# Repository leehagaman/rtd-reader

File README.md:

# 16 Channel PT1000 Reader

This project describes an Arduino shield which allows the reading of up to 16 PT1000 2 wire RTD temperature sensors, and communicate that information to a computer. It also has two digital outputs, designed to control relays which can turn heaters on and off. This design allows the Arduino to autonomously control the heaters, ensuring consistent temperature control even if the main computer loses connection.

## Getting Started

### Materials

To make the Arduino shield, you need the following items:

- 1 Arduino Due or Arduino Mega (with corresponding cable, and power supply if you'd like continued operation in the event of a computer failure)
- 1 Printed Circuit Board (see .brd file)
- 1 LM324 Op Amp chip [link](https://www.digikey.com/product-detail/en/texas-instruments/LM324N/296-1391-5-ND/277627)
- 3 CD4052B Multiplexing chips [link](https://www.digikey.com/product-detail/en/texas-instruments/CD4051BE/296-2057-5-ND/67305)
- 18 0.1" double right angle connectors [link](https://www.digikey.com/products/en?mpart=PREC040SFAN-RC&v=35)
- 40 0.1" straight connectors [link](https://www.digikey.com/products/en?mpart=PREC040SFAN-RC&v=35)
- 16 1kΩ resistors
- 6 amplification resistors (optional, see "choosing resistors" section)

### Choosing Resistors

For the 16 1kΩ resistors, you can measure and record their specific resistances after installation for increased accuracy, so there is no special process to choose them.

The Arduino will constantly measure an unamplified temperature, which has a resolution which varies from about 0.1°C near -200°C, to about 1°C near 40°C (this is calculated using 10 bit resolution, an Arduino Due can be configured to use 12 bits instead, giving 100 times finer resolution). 

<p align="center">Serial monitor output comparing amplified and unamplified measurements. These curves were obtained by pinching a PT1000 with my fingers and then releasing. The overall offset can likely be fixed with calibration. (Image will be updated to a cleaner one soon.)</p>

To improve this resolution, the Arduino will also measure an amplified temperature, which lets you effectively "zoom in" on an specific temperature range (see above comparison). There is a several step process to determine the ideal resistors for a given temperature range of interest.

1. Decide on T<sub>min</sub> and T<sub>max</sub>, the minimum and maximum temperatures you plan to measure with your amplified circuit.
2. Calculate the R<sub>min</sub> and R<sub>max</sub>, the corresponding minimum and maximum PT1000 resistances (use something like [this table](https://web.mst.edu/~cottrell/ME240/Resources/Temperature/RTD%20table.pdf))
3. Calculate V<sub>min</sub> and V<sub>max</sub>, the corresponding voltages read by the Arduino. Use the formula V=R/(R+1000Ω)*(3.3 Volts).
4. We have our unamplified voltage range, and we will use our amplifier to convert this to our desired voltage range of 0.1V-1.7V (the op-amp only gets within 1.5V of the maximum, so the measurable range is 0-1.8V, and we give each side 0.1V of buffer). So, the desired amplification factor is A=(V<sub>max</sub>- V<sub>min</sub>)/(1.6 Volts). We also have an ideal offset voltage V<sub>off</sub>  equal to V<sub>min</sub>.
5. Now that we have ideal A and V<sub>off</sub> values chosen, we must modify them to make their values easy to construct with available resistors. We must choose resistors with resistance values R<sub>1</sub>, R<sub>2</sub>, R<sub>off1</sub>, and R<sub>off2</sub> such that A=R<sub>2</sub>/R<sub>1</sub> and  V<sub>off</sub>=V<sub>min</sub>. It is perfectly fine to decrease A and adjust V<sub>off</sub> in order to accomplish this without having to use nonstandard resistors, it will just slightly change the range of voltages, which is why we gave each side 0.1V of buffer in step 4. 
6. To check that your resistance values will work as expected, recalculate your amplified voltage range. The amplified voltage will be V<sub>amp </sub>= R<sub>2</sub>/R<sub>1</sub> * (V - (3.3 Volts) * R<sub>off2</sub> / (R<sub>off1</sub> + R<sub>off2</sub> )) where V is the unamplified voltage. It's a good idea to use that formula to double check that the amplified voltage will stay in the range 0 to 1.7 Volts for the expected unamplified voltages from step 3.

Now that we have our desired resistor values, R<sub>1</sub>, R<sub>2</sub>, R<sub>off1</sub>, and R<sub>off2</sub>, we need to choose resistors with those resistance values. We need a pair of resistors, R<sub>amp1</sub> and R<sub>amp2</sub>, to have resistances as close as possible to R<sub>1</sub>, and another pair R<sub>amp3</sub> and R<sub>amp4</sub>, to have resistances as close as possible to R<sub>amp1</sub> and R<sub>2</sub>. It is worth taking some time to match the resistances of each pair, as the linearity of the amplifier depends on their values being equal. Once you have also chosen R<sub>off1</sub> and R<sub>off2</sub>, take the time to measure and record the resistances of each resistor, as their precise values are used by the arduino program to reconstruct the temperature from the amplified voltage, and the resistances cannot be simply measured after soldering.

### Assembly

Soldering can be done in any order, but I recommend soldering the pin connectors last as they can give you less room to solder the 16 1kΩ resistors.

### Program Modification

In the Arduino file, you should modify the parameters to correspond to your measured resistances and active channels. You can also switch between LabVIEW output and serial monitor output.

I plan to improve the readability of the arduino code once the LabVIEW integration is finalized.

### Calibration

Will be updated soon. I should be able to use a known temperature to calibrate the temperature measurements, as well as matching the amplified measurement to the unamplified measurement just using the ambient room temperature.

## LabVIEW Integration

Will be updated soon. I plan to support output of temperature as well as input of desired temperature windows.

## Acknowledgments

* Domenico Franco helped me iterate the PCB design.

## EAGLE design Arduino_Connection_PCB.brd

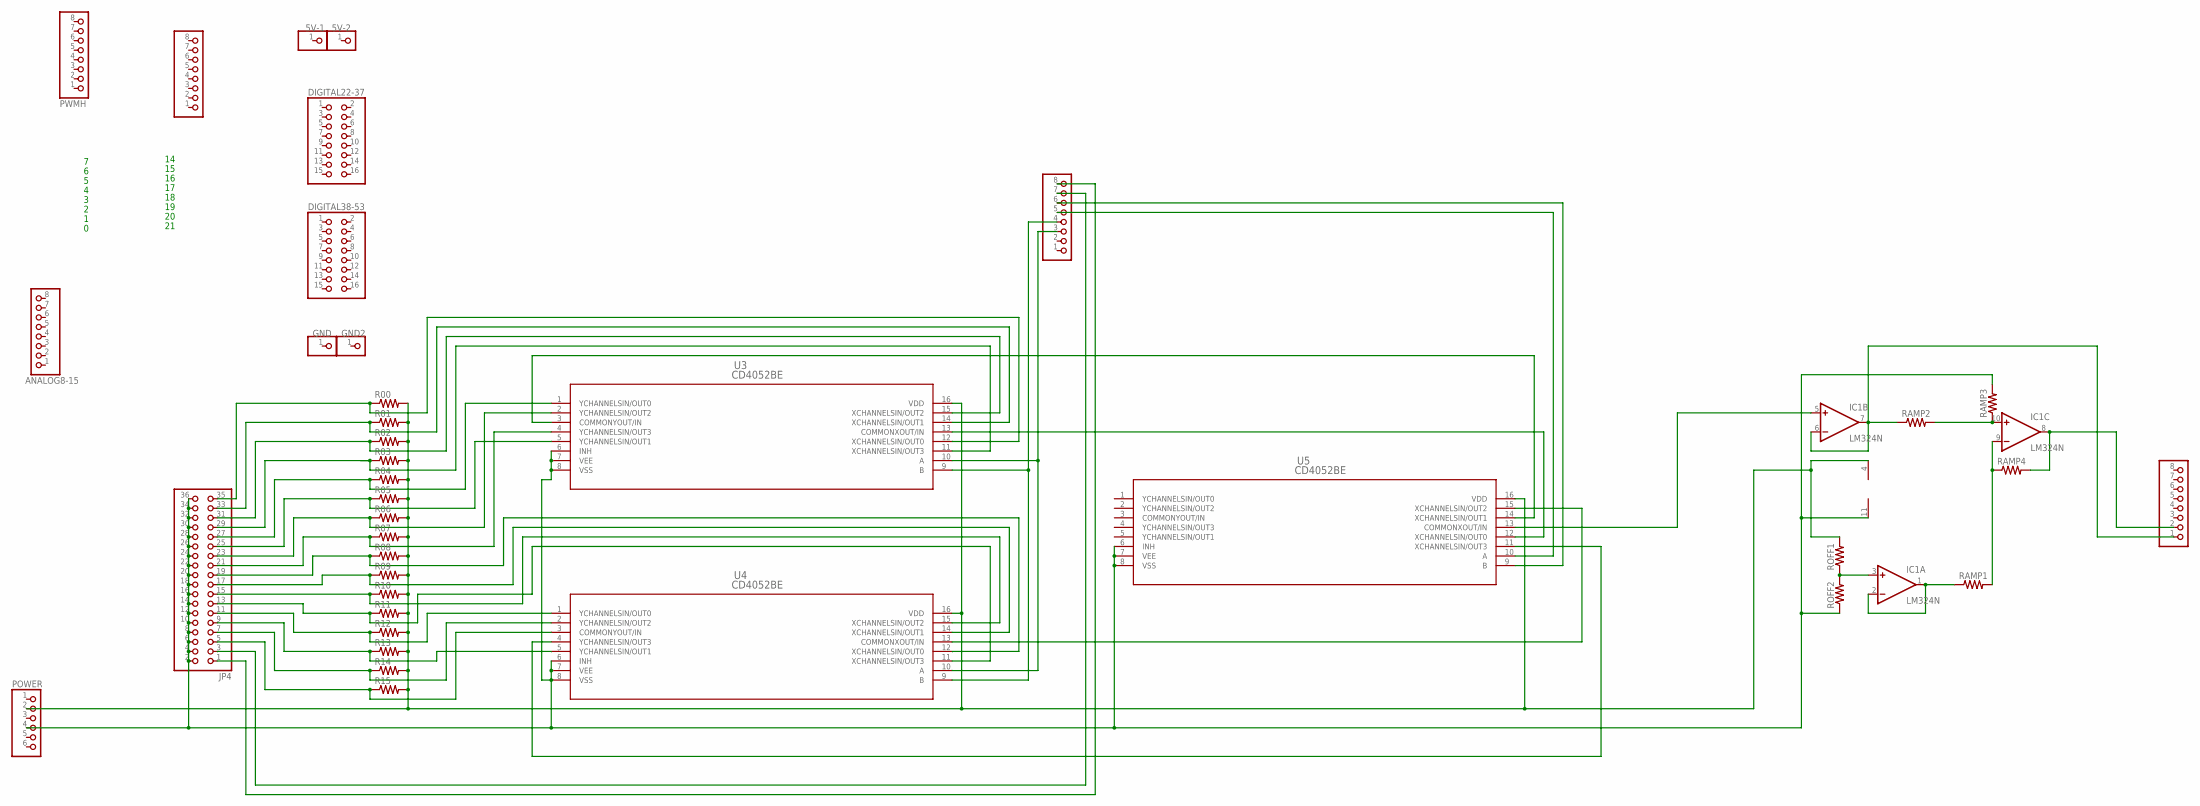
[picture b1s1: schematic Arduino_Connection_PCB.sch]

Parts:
5V-1, 5V-2: PINHD-1X1; 1X01
ANALOG0-7, ANALOG8-15: PINHD-1X8; 1X08
COMMUNICATION: PINHD-1X8; 1X08
DIGITAL22-37, DIGITAL38-53: PINHD-2X8; 2X08
GND, GND2: PINHD-1X1; 1X01
IC1: LM324N; DIL14
JP4: PINHD-2X18/90; 2X18/90
POWER: PINHD-1X6; 1X06
PWMH: PINHD-1X8; 1X08
PWML: PINHD-1X8; 1X08
R00, R01, R02, R03, R04, R05, R06, R07, R08, R09, R10, R11, R12, R13, R14, R15: R-US_0204/7; 0204/7
RAMP1, RAMP2, RAMP3, RAMP4: R-US_0204/7; 0204/7
ROFF1, ROFF2: R-US_0204/7; 0204/7
U3, U4, U5: CD4052BE; N16

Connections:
unnamed: IC1.5 (+IN), U5.13 (COMMONXOUT/IN)
unnamed: ANALOG0-7.1, IC1.6 (-IN), IC1.7 (OUT), RAMP2.1
unnamed: JP4.3, PWML.7
unnamed: JP4.1, PWML.8
unnamed: IC1.3 (+IN), ROFF1.1, ROFF2.2
unnamed: IC1.11 (V-), JP4.2, JP4.4, JP4.6, JP4.8, JP4.10, JP4.12, JP4.14, JP4.16, JP4.18, JP4.20, JP4.22, JP4.24, JP4.26, JP4.28, JP4.30, JP4.32, JP4.34, JP4.36, POWER.4, RAMP3.2, ROFF2.1, U3.6 (INH), U3.7 (VEE), U3.8 (VSS), U4.6 (INH), U4.7 (VEE), U4.8 (VSS), U5.6 (INH), U5.7 (VEE), U5.8 (VSS)
unnamed: JP4.13, R11.1, U4.11 (XCHANNELSIN/OUT3)
unnamed: PWML.3, U3.10 (A), U4.10 (A)
unnamed: IC1.4 (V+), POWER.2, R00.2, R01.2, R02.2, R03.2, R04.2, R05.2, R06.2, R07.2, R08.2, R09.2, R10.2, R11.2, R12.2, R13.2, R14.2, R15.2, ROFF1.2, U3.16 (VDD), U4.16 (VDD), U5.16 (VDD)
unnamed: JP4.25, R05.1, U3.5 (YCHANNELSIN/OUT1)
unnamed: JP4.35, R00.1, U3.12 (XCHANNELSIN/OUT0)
unnamed: PWML.4, U3.9 (B), U4.9 (B)
unnamed: JP4.19, R08.1, U4.12 (XCHANNELSIN/OUT0)
unnamed: JP4.21, R07.1, U3.4 (YCHANNELSIN/OUT3)
unnamed: JP4.17, R09.1, U4.14 (XCHANNELSIN/OUT1)
unnamed: JP4.5, R15.1, U4.3 (COMMONYOUT/IN)
unnamed: JP4.7, R14.1, U4.2 (YCHANNELSIN/OUT2)
unnamed: JP4.9, R13.1, U4.5 (YCHANNELSIN/OUT1)
unnamed: JP4.11, R12.1, U4.1 (YCHANNELSIN/OUT0)
unnamed: PWML.5, U5.10 (A)
unnamed: JP4.15, R10.1, U4.15 (XCHANNELSIN/OUT2)
unnamed: PWML.6, U5.9 (B)
unnamed: IC1.1 (OUT), IC1.2 (-IN), RAMP1.1
unnamed: IC1.9 (-IN), RAMP1.2, RAMP4.1
unnamed: IC1.10 (+IN), RAMP2.2, RAMP3.1
unnamed: ANALOG0-7.2, IC1.8 (OUT), RAMP4.2
unnamed: U3.13 (COMMONXOUT/IN), U5.12 (XCHANNELSIN/OUT0)
unnamed: U3.3 (COMMONYOUT/IN), U5.14 (XCHANNELSIN/OUT1)
unnamed: U4.13 (COMMONXOUT/IN), U5.15 (XCHANNELSIN/OUT2)
unnamed: U4.4 (YCHANNELSIN/OUT3), U5.11 (XCHANNELSIN/OUT3)
unnamed: JP4.31, R02.1, U3.15 (XCHANNELSIN/OUT2)
unnamed: JP4.27, R04.1, U3.1 (YCHANNELSIN/OUT0)
unnamed: JP4.23, R06.1, U3.2 (YCHANNELSIN/OUT2)
unnamed: JP4.29, R03.1, U3.11 (XCHANNELSIN/OUT3)
unnamed: JP4.33, R01.1, U3.14 (XCHANNELSIN/OUT1)

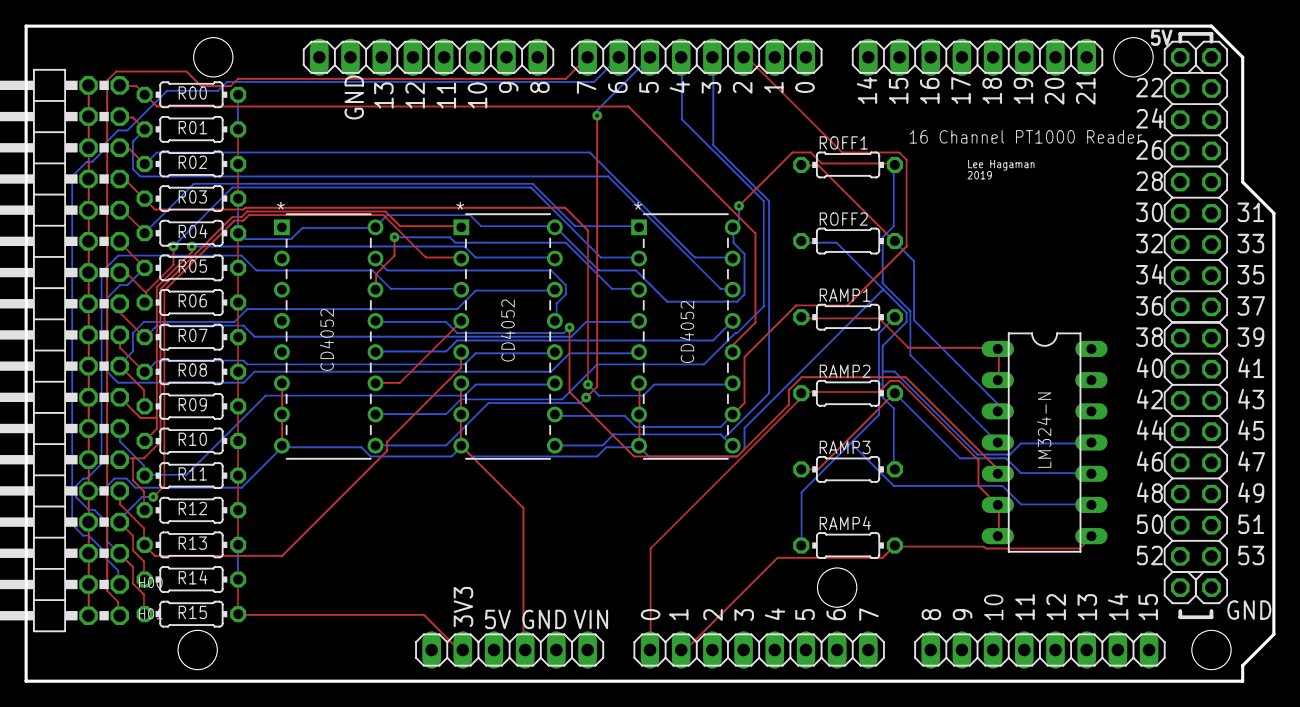
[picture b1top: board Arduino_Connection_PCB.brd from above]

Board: 2 copper layers, 101.6 x 53.3 mm, 39 parts (0 on the bottom side), 35 nets.

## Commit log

2020-05-11 fixed README image sources
2020-05-11 removed latex from README
2020-05-11 fixed README image sizes
2020-05-11 fixed README centering
2020-05-11 fixed README centering again
